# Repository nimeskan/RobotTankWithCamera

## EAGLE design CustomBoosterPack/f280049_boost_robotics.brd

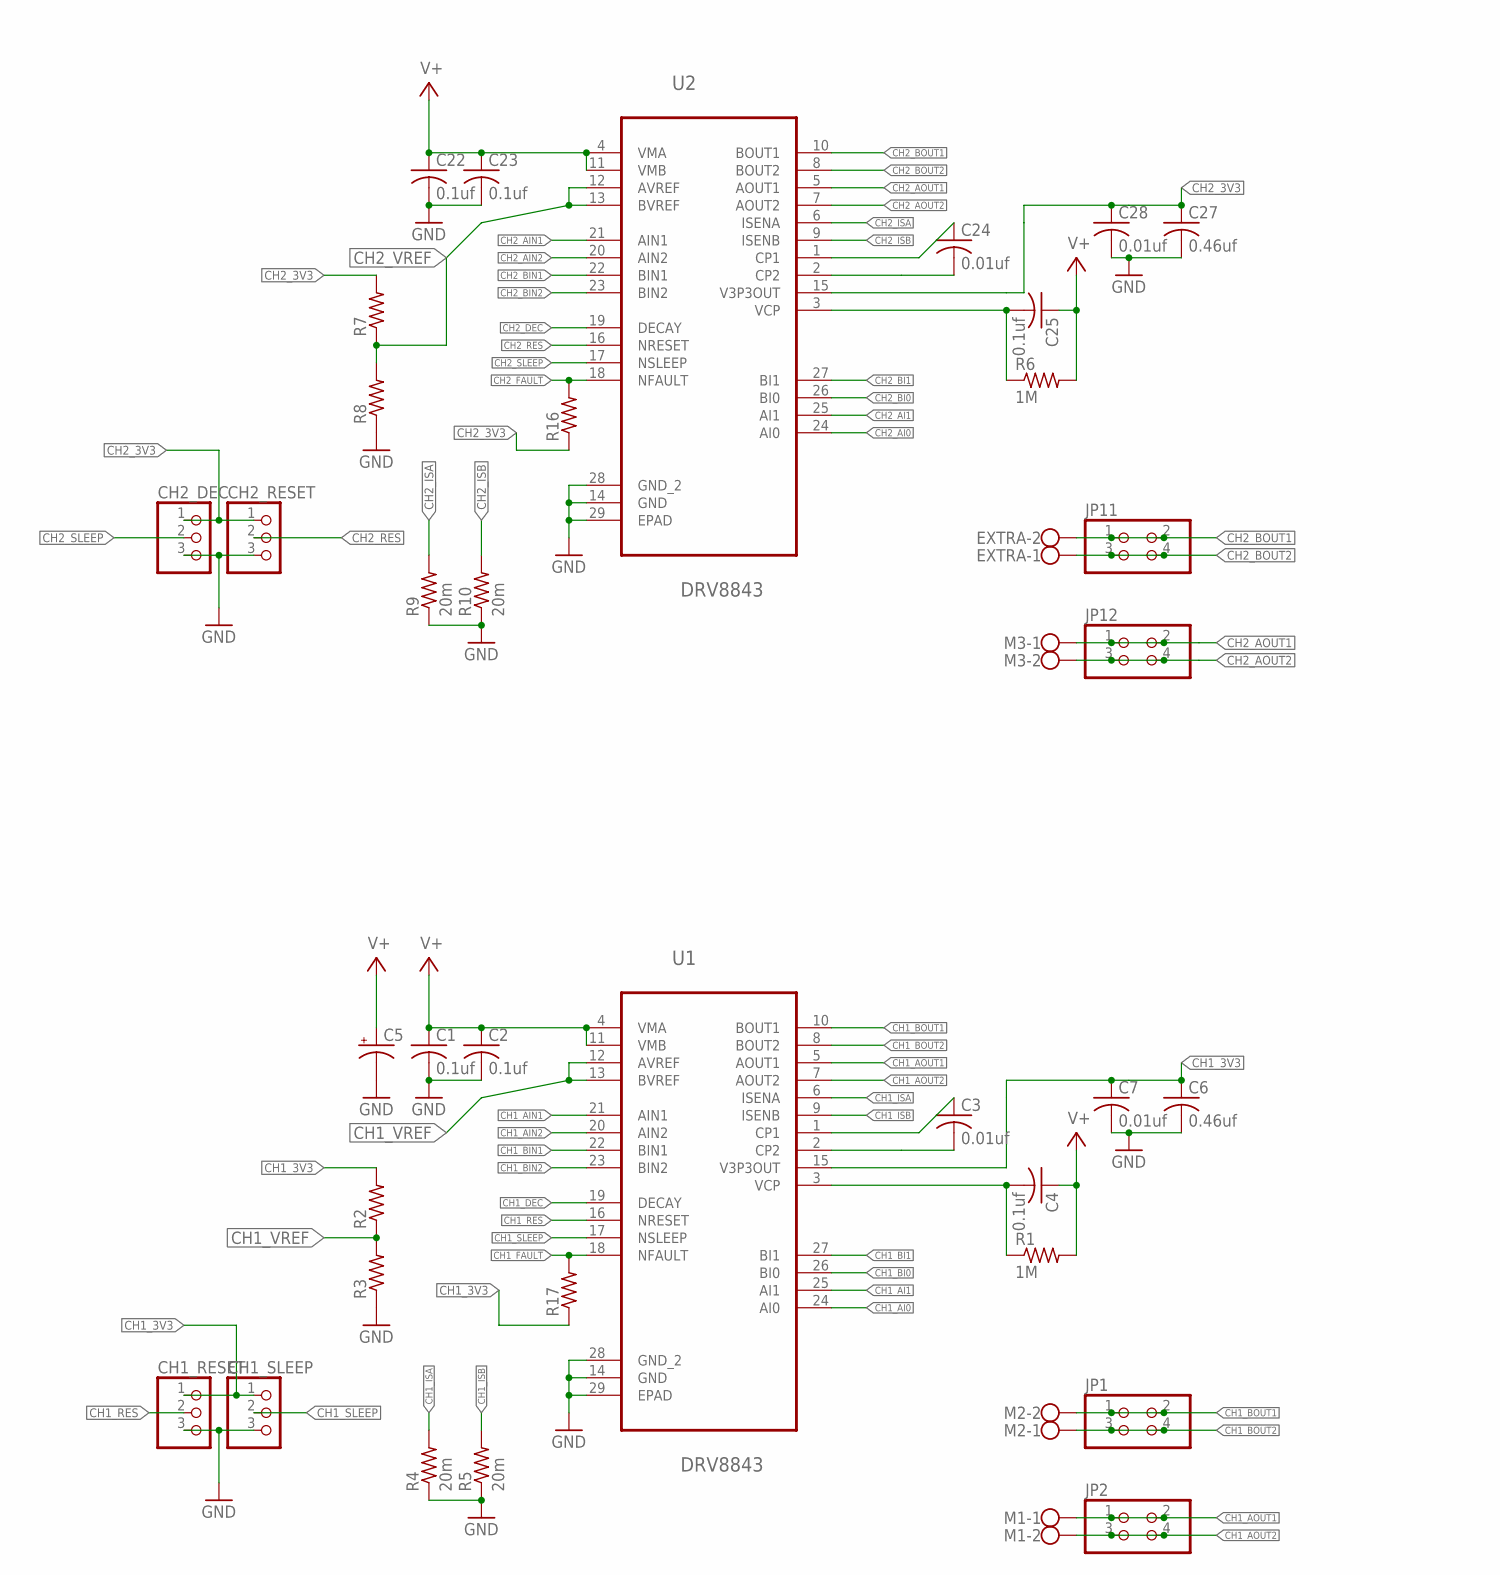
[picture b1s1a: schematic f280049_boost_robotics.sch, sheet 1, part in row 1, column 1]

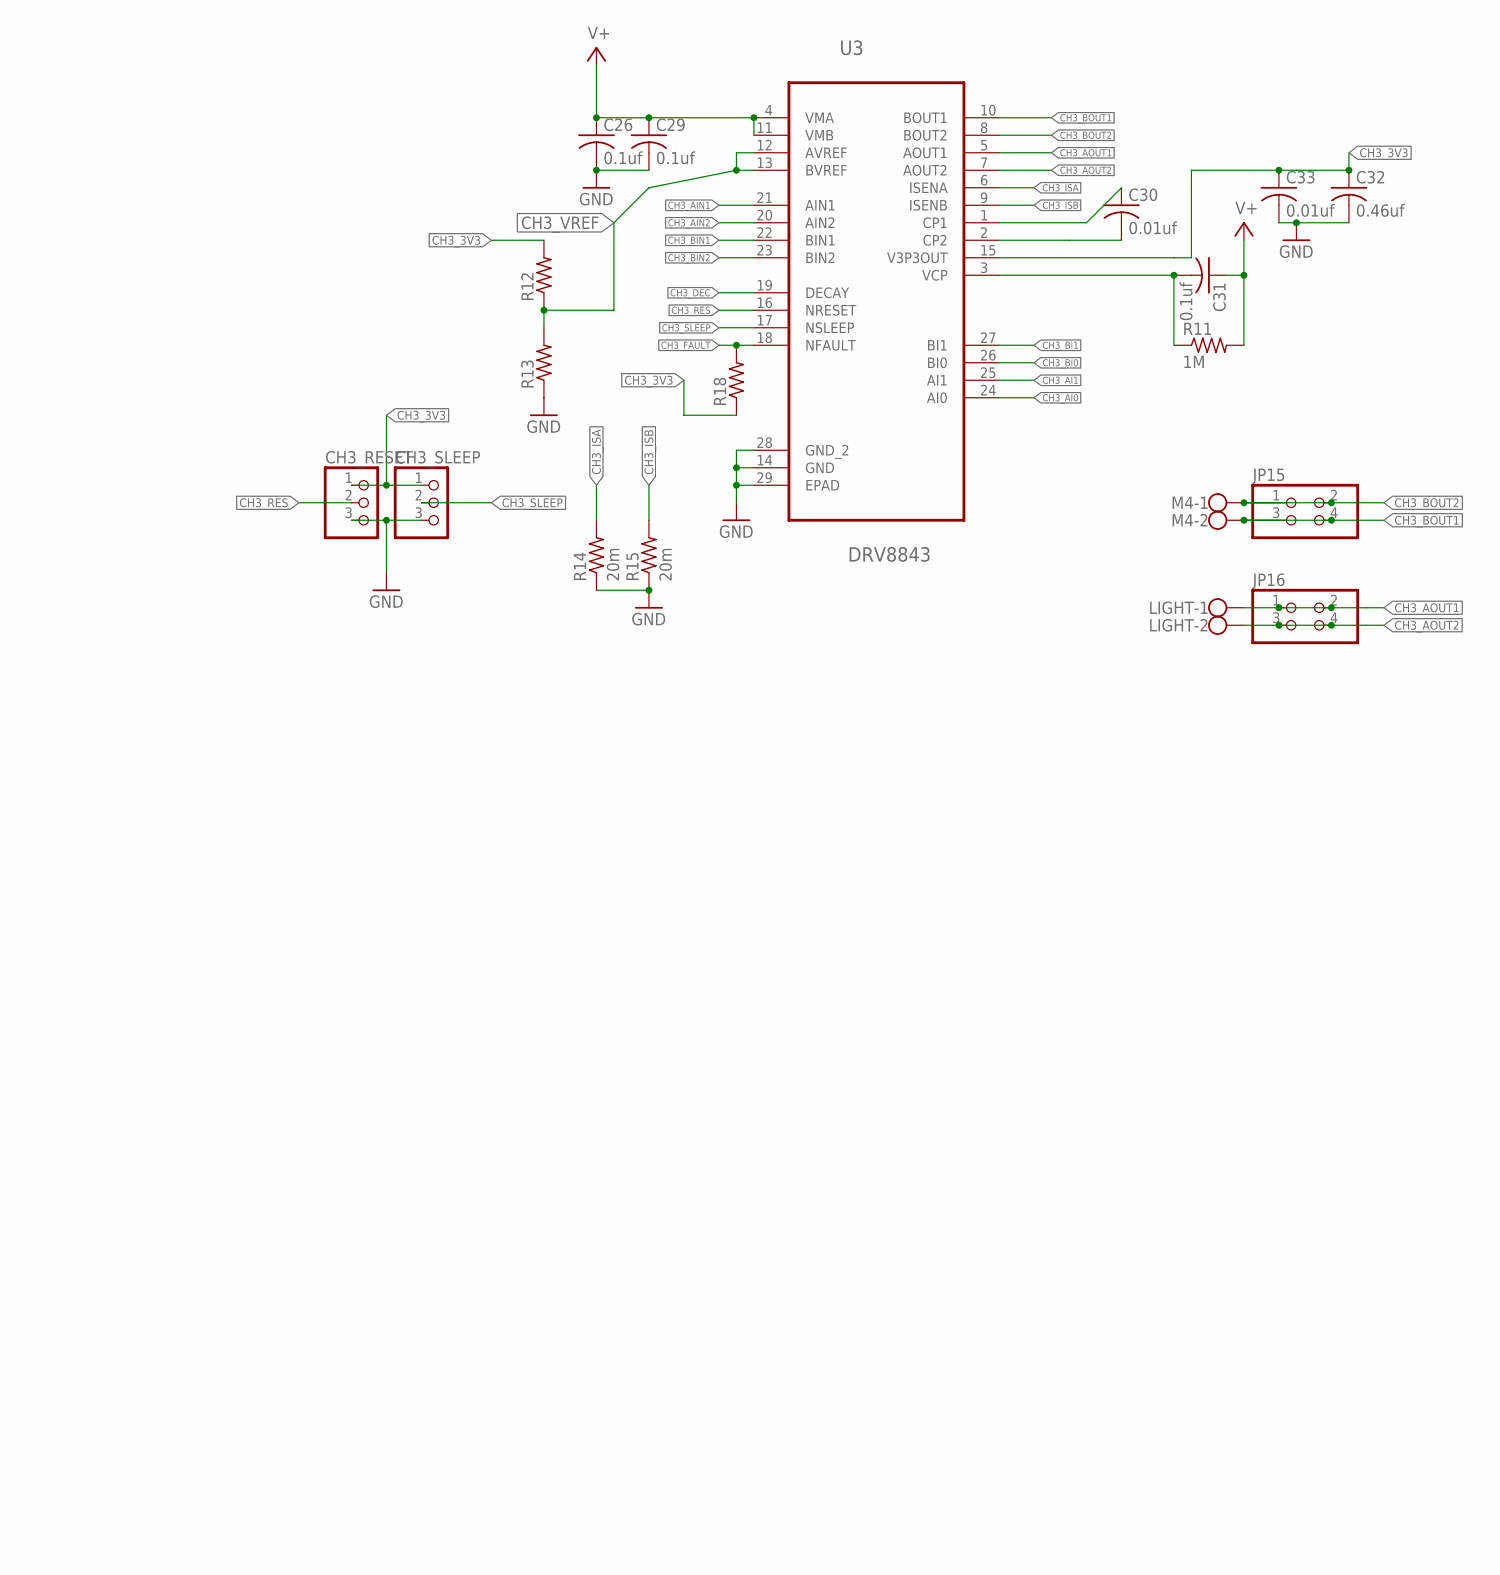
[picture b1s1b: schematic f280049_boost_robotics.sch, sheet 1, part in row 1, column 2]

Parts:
C1, C2, C4, C22, C23, C25, C26, C29, C31: 0.1uf; C0603K
C3, C7, C24, C28, C30, C33: 0.01uf; C0603K
C5: CPOL-USE5-8.5; E5-8,5
C6, C27, C32: 0.46uf; C0603K
CH1_RESET, CH1_SLEEP, CH2_DEC, CH2_RESET, CH3_RESET, CH3_SLEEP: PINHD-1X3; 1X03
EXTRA: W237-102
JP1, JP2, JP11, JP12, JP15, JP16: PINHD-2X2; 2X02
LIGHT: W237-102
M1, M2, M3, M4: W237-102
R1, R6, R11: 1M; R0402
R2, R3, R7, R8, R12, R13, R16, R17, R18: R-US_R0402; R0402
R4, R5, R9, R10, R14, R15: 20m; R0402
U1, U2, U3: DRV8843; SOP65P640X120-29N

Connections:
CH1_3V3: C6.1, C7.1, CH1_RESET.1, CH1_SLEEP.1, R2.2, R17.1, U1.15 (V3P3OUT)
CH1_AI0: U1.24 (AI0); also elsewhere on the board
CH1_AI1: U1.25 (AI1); also elsewhere on the board
CH1_AIN1: U1.21 (AIN1); also elsewhere on the board
CH1_AIN2: U1.20 (AIN2); also elsewhere on the board
CH1_AOUT1: JP2.1, JP2.2, M1.1, U1.5 (AOUT1)
CH1_AOUT2: JP2.3, JP2.4, M1.2, U1.7 (AOUT2)
CH1_BI0: U1.26 (BI0); also elsewhere on the board
CH1_BI1: U1.27 (BI1); also elsewhere on the board
CH1_BIN1: U1.22 (BIN1); also elsewhere on the board
CH1_BIN2: U1.23 (BIN2); also elsewhere on the board
CH1_BOUT1: JP1.1, JP1.2, M2.2, U1.10 (BOUT1)
CH1_BOUT2: JP1.3, JP1.4, M2.1, U1.8 (BOUT2)
CH1_DEC: U1.19 (DECAY); also elsewhere on the board
CH1_FAULT: R17.2, U1.18 (NFAULT); also elsewhere on the board
CH1_ISA: R4.2, U1.6 (ISENA)
CH1_ISB: R5.2, U1.9 (ISENB)
CH1_RES: CH1_RESET.2, U1.16 (NRESET)
CH1_SLEEP: CH1_SLEEP.2, U1.17 (NSLEEP)
CH1_VREF: R2.1, R3.2, U1.12 (AVREF), U1.13 (BVREF)
CH2_3V3: C27.1, C28.1, CH2_DEC.1, CH2_RESET.1, R7.2, R16.1, U2.15 (V3P3OUT)
CH2_AI0: U2.24 (AI0); also elsewhere on the board
CH2_AI1: U2.25 (AI1); also elsewhere on the board
CH2_AIN1: U2.21 (AIN1); also elsewhere on the board
CH2_AIN2: U2.20 (AIN2); also elsewhere on the board
CH2_AOUT1: JP12.1, JP12.2, M3.1, U2.5 (AOUT1)
CH2_AOUT2: JP12.3, JP12.4, M3.2, U2.7 (AOUT2)
CH2_BI0: U2.26 (BI0); also elsewhere on the board
CH2_BI1: U2.27 (BI1); also elsewhere on the board
CH2_BIN1: U2.22 (BIN1); also elsewhere on the board
CH2_BIN2: U2.23 (BIN2); also elsewhere on the board
CH2_BOUT1: EXTRA.2, JP11.1, JP11.2, U2.10 (BOUT1)
CH2_BOUT2: EXTRA.1, JP11.3, JP11.4, U2.8 (BOUT2)
CH2_DEC: U2.19 (DECAY); also elsewhere on the board
CH2_FAULT: R16.2, U2.18 (NFAULT); also elsewhere on the board
CH2_ISA: R9.2, U2.6 (ISENA)
CH2_ISB: R10.2, U2.9 (ISENB)
CH2_RES: CH2_RESET.2, U2.16 (NRESET)
CH2_SLEEP: CH2_DEC.2, U2.17 (NSLEEP)
CH2_VREF: R7.1, R8.2, U2.12 (AVREF), U2.13 (BVREF)
CH3_3V3: C32.1, C33.1, CH3_RESET.1, CH3_SLEEP.1, R12.2, R18.1, U3.15 (V3P3OUT)
CH3_AI0: U3.24 (AI0)
CH3_AI1: U3.25 (AI1)
CH3_AIN1: U3.21 (AIN1); also elsewhere on the board
CH3_AIN2: U3.20 (AIN2); also elsewhere on the board
CH3_AOUT1: JP16.1, JP16.2, LIGHT.1, U3.5 (AOUT1)
CH3_AOUT2: JP16.3, JP16.4, LIGHT.2, U3.7 (AOUT2)
CH3_BI0: U3.26 (BI0)
CH3_BI1: U3.27 (BI1)
CH3_BIN1: U3.22 (BIN1); also elsewhere on the board
CH3_BIN2: U3.23 (BIN2); also elsewhere on the board
CH3_BOUT1: JP15.3, JP15.4, M4.2, U3.10 (BOUT1)
CH3_BOUT2: JP15.1, JP15.2, M4.1, U3.8 (BOUT2)
CH3_DEC: U3.19 (DECAY); also elsewhere on the board
CH3_FAULT: R18.2, U3.18 (NFAULT); also elsewhere on the board
CH3_ISA: R14.2, U3.6 (ISENA)
CH3_ISB: R15.2, U3.9 (ISENB)
CH3_RES: CH3_RESET.2, U3.16 (NRESET)
CH3_SLEEP: CH3_SLEEP.2, U3.17 (NSLEEP)
CH3_VREF: R12.1, R13.2, U3.12 (AVREF), U3.13 (BVREF)
GND: C1.2, C2.2, C5.-, C6.2, C7.2, C22.2, C23.2, C26.2, C27.2, C28.2, C29.2, C32.2, C33.2, CH1_RESET.3, CH1_SLEEP.3, CH2_DEC.3, CH2_RESET.3, CH3_RESET.3, CH3_SLEEP.3, R3.1, R4.1, R5.1, R8.1, R9.1, R10.1, R13.1, R14.1, R15.1, U1.14 (GND), U1.28 (GND_2), U1.29 (EPAD), U2.14 (GND), U2.28 (GND_2), U2.29 (EPAD), U3.14 (GND), U3.28 (GND_2), U3.29 (EPAD); also elsewhere on the board
unnamed: C3.1, U1.1 (CP1)
unnamed: C3.2, U1.2 (CP2)
unnamed: C4.2, R1.1, U1.3 (VCP)
unnamed: C24.1, U2.1 (CP1)
unnamed: C24.2, U2.2 (CP2)
unnamed: C25.2, R6.1, U2.3 (VCP)
unnamed: C30.1, U3.1 (CP1)
unnamed: C30.2, U3.2 (CP2)
unnamed: C31.2, R11.1, U3.3 (VCP)
V+: C1.1, C2.1, C4.1, C5.+, C22.1, C23.1, C25.1, C26.1, C29.1, C31.1, R1.2, R6.2, R11.2, U1.4 (VMA), U1.11 (VMB), U2.4 (VMA), U2.11 (VMB), U3.4 (VMA), U3.11 (VMB); also elsewhere on the board

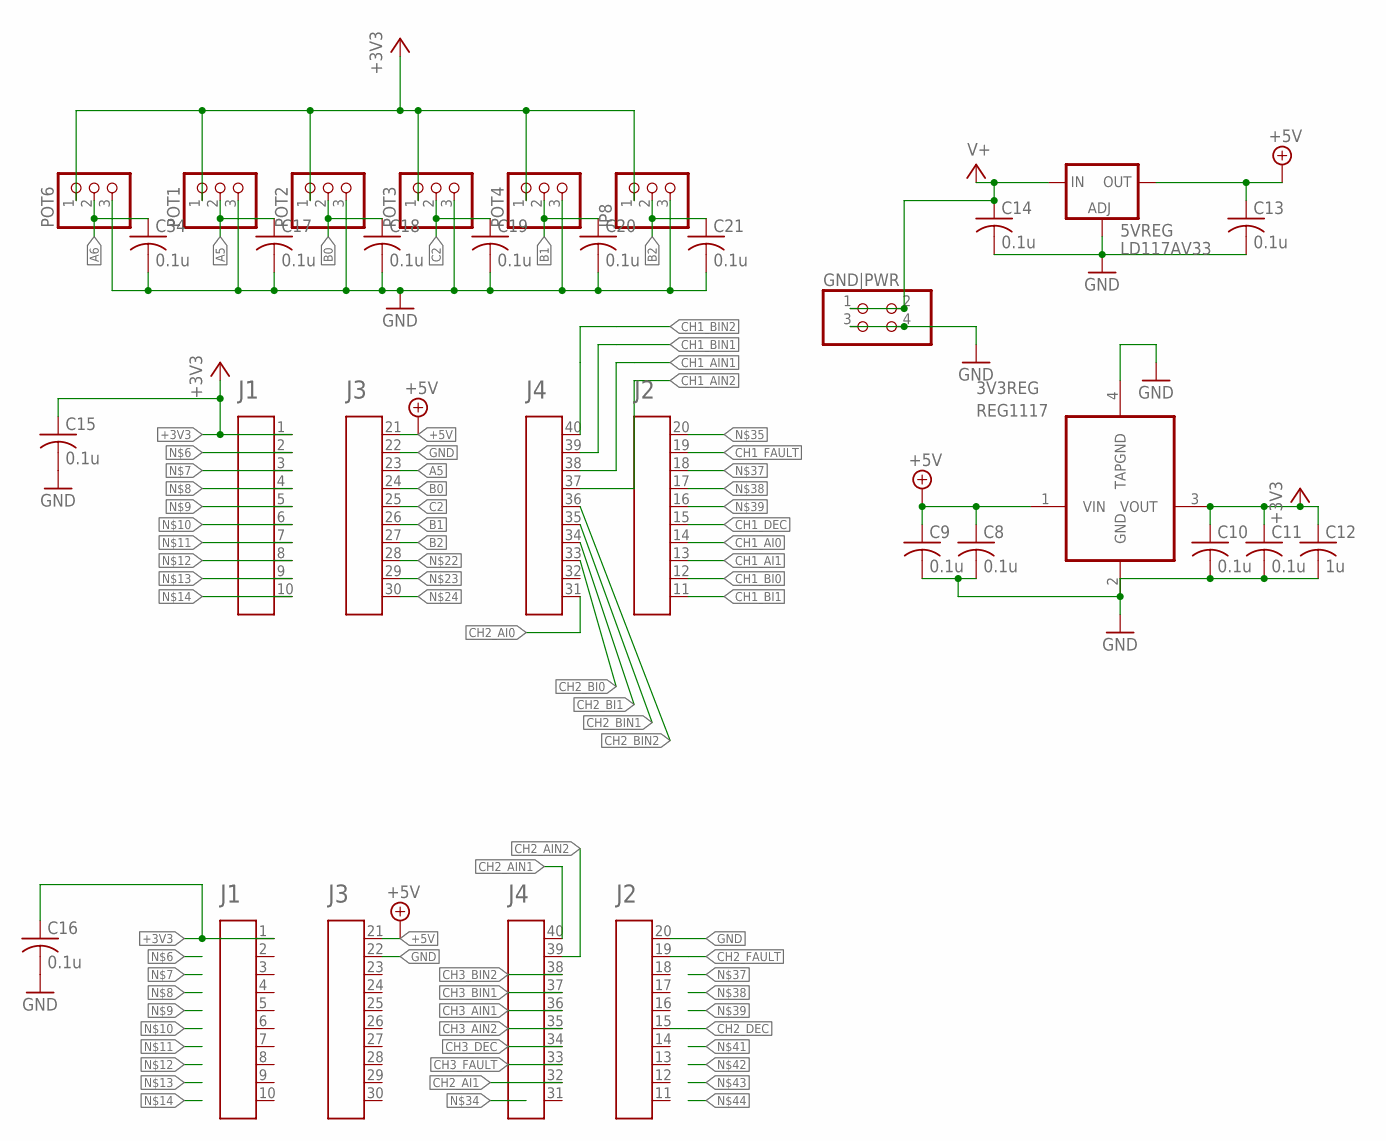
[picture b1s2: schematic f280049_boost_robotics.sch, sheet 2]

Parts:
3V3REG: REG1117; SOT223
5VREG: LD117AV33; TO220L1
A1, A2: HEADER4X10-BOOSTERPACK; 4X10-BOOSTERPACK
C8, C9, C10, C11, C13, C14, C15, C16, C17, C18, C19, C20, C21, C34: 0.1u; C0603K
C12: 1u; C0805K
GND|PWR: PINHD-2X2; 2X02
JP8: PINHD-1X3; 1X03
POT1, POT2, POT3, POT4, POT6: PINHD-1X3; 1X03

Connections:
+3V3: 3V3REG.3 (VOUT), A1.1, A2.1, C10.1, C11.1, C12.1, C15.1, C16.1, JP8.1, POT1.1, POT2.1, POT3.1, POT4.1, POT6.1
+5V: 3V3REG.1 (VIN), 5VREG.2 (OUT), A1.21, A2.21, C8.1, C9.1, C13.1
A5: A2.23, C17.1, POT1.2
A6: C34.1, POT6.2
B0: A2.24, C18.1, POT2.2
B1: A2.26, C20.1, POT4.2
B2: A2.27, C21.1, JP8.2
C2: A2.25, C19.1, POT3.2
CH1_AI0: A2.14; also elsewhere on the board
CH1_AI1: A2.13; also elsewhere on the board
CH1_AIN1: A2.38; also elsewhere on the board
CH1_AIN2: A2.37; also elsewhere on the board
CH1_BI0: A2.12; also elsewhere on the board
CH1_BI1: A2.11; also elsewhere on the board
CH1_BIN1: A2.39; also elsewhere on the board
CH1_BIN2: A2.40; also elsewhere on the board
CH1_DEC: A2.15; also elsewhere on the board
CH1_FAULT: A2.19; also elsewhere on the board
CH2_AI0: A2.31; also elsewhere on the board
CH2_AI1: A1.32; also elsewhere on the board
CH2_AIN1: A1.40; also elsewhere on the board
CH2_AIN2: A1.39; also elsewhere on the board
CH2_BI0: A2.33; also elsewhere on the board
CH2_BI1: A2.34; also elsewhere on the board
CH2_BIN1: A2.35; also elsewhere on the board
CH2_BIN2: A2.36; also elsewhere on the board
CH2_DEC: A1.15; also elsewhere on the board
CH2_FAULT: A1.19; also elsewhere on the board
CH3_AIN1: A1.36; also elsewhere on the board
CH3_AIN2: A1.35; also elsewhere on the board
CH3_BIN1: A1.37; also elsewhere on the board
CH3_BIN2: A1.38; also elsewhere on the board
CH3_DEC: A1.34; also elsewhere on the board
CH3_FAULT: A1.33; also elsewhere on the board
GND: 3V3REG.2 (GND), 3V3REG.4 (TAPGND), 5VREG.1 (ADJ), A1.20, A1.22, A2.22, C8.2, C9.2, C10.2, C11.2, C12.2, C13.2, C14.2, C15.2, C16.2, C17.2, C18.2, C19.2, C20.2, C21.2, C34.2, GND|PWR.3, GND|PWR.4, JP8.3, POT1.3, POT2.3, POT3.3, POT4.3, POT6.3; also elsewhere on the board
V+: 5VREG.3 (IN), C14.1, GND|PWR.1, GND|PWR.2; also elsewhere on the board

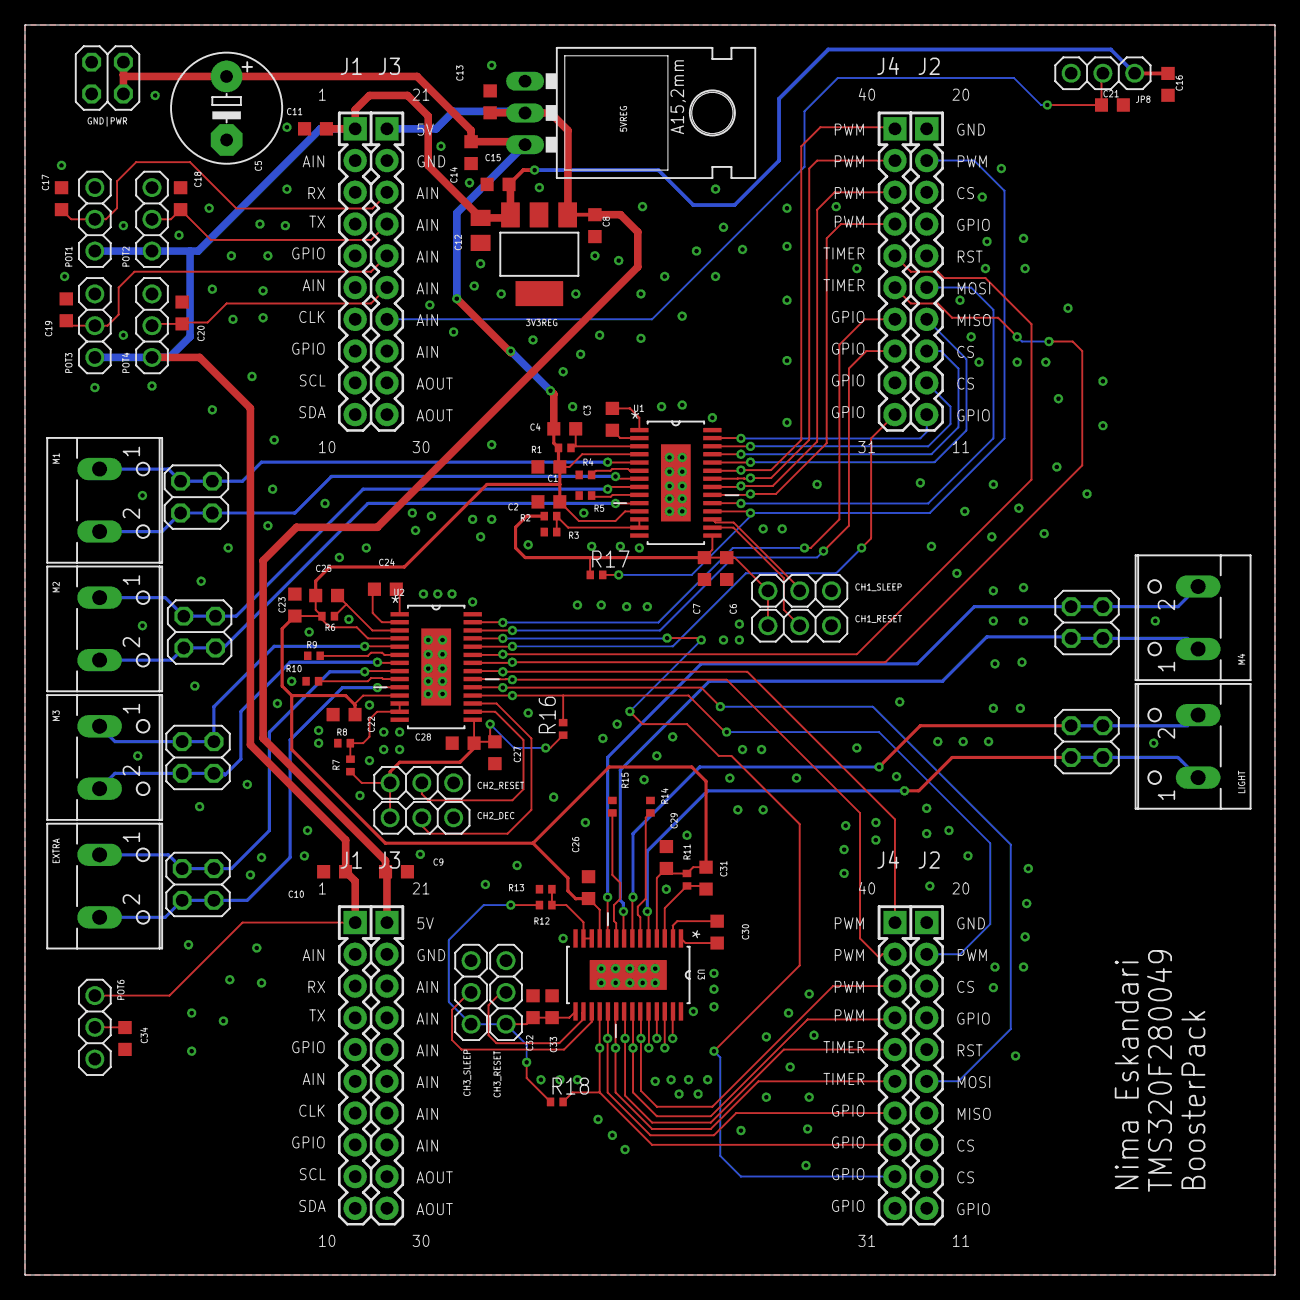
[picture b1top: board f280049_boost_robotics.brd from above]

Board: 2 copper layers, 100.0 x 100.0 mm, 84 parts (0 on the bottom side), 75 nets.

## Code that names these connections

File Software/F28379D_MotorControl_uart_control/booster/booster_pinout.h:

/*
 * booster_pinout.h
 *
 *  Created on: Sep 14, 2018
 *      Author: a0225962
 */

#ifndef BOOSTER_PINOUT_H_
#define BOOSTER_PINOUT_H_

// PINMAP

// CHANNEL1
#define CH1_BIN2                0
#define CH1_BIN1                1

#define CH1_AIN2                3
#define CH1_AIN1                2

#define CH1_DEC                 58
#define CH1_FAULT               61

#define CH1_BI1                 29
#define CH1_BI0                 125

#define CH1_AI1                 124
#define CH1_AI0                 59

#define CH1_BIN2_CONFIG         GPIO_0_EPWM1A
#define CH1_BIN1_CONFIG         GPIO_1_EPWM1B

#define CH1_AIN2_CONFIG         GPIO_3_EPWM2B
#define CH1_AIN1_CONFIG         GPIO_2_EPWM2A

#define CH1_DEC_CONFIG          GPIO_58_GPIO58
#define CH1_FAULT_CONFIG        GPIO_61_GPIO61

#define CH1_BI1_CONFIG          GPIO_29_GPIO29
#define CH1_BI0_CONFIG          GPIO_125_GPIO125

#define CH1_AI1_CONFIG          GPIO_124_GPIO124
#define CH1_AI0_CONFIG          GPIO_59_GPIO59

// CHANNEL 2
#define CH2_BIN2                4
#define CH2_BIN1                5

#define CH2_AIN2                6
#define CH2_AIN1                7

#define CH2_DEC                 63
#define CH2_FAULT               66

#define CH2_BI1                 24
#define CH2_BI0                 16

//#define CH2_AI1                 DAC3
//#define CH2_AI0                 DAC2

#define CH2_BIN2_CONFIG         GPIO_4_EPWM3A
#define CH2_BIN1_CONFIG         GPIO_5_EPWM3B

#define CH2_AIN2_CONFIG         GPIO_6_EPWM4A
#define CH2_AIN1_CONFIG         GPIO_7_EPWM4B

#define CH2_DEC_CONFIG          GPIO_63_GPIO63
#define CH2_FAULT_CONFIG        GPIO_66_GPIO66

#define CH2_BI1_CONFIG          GPIO_24_GPIO24
#define CH2_BI0_CONFIG          GPIO_16_GPIO16

//#define CH2_AI1_CONFIG          GPIO_14_GPIO14
//#define CH2_AI0_CONFIG          GPIO_25_GPIO25

// CHANNEL 3
#define CH3_BIN2                8
#define CH3_BIN1                9

#define CH3_AIN2                11
#define CH3_AIN1                10

#define CH3_DEC                 14
#define CH3_FAULT               15

#define CH3_BIN2_CONFIG         GPIO_8_EPWM5A
#define CH3_BIN1_CONFIG         GPIO_9_EPWM5B

#define CH3_AIN2_CONFIG         GPIO_11_EPWM6B
#define CH3_AIN1_CONFIG         GPIO_10_EPWM6A

#define CH3_DEC_CONFIG          GPIO_14_GPIO14
#define CH3_FAULT_CONFIG        GPIO_15_GPIO15

// EQEPs
// Channel1
#define CH1_EQEPA               20
#define CH1_EQEPB               21
#define CH1_EQEPI               99

#define CH2_EQEPA               54
#define CH2_EQEPB               55
#define CH2_EQEPI               57

#define CH1_EQEPA_CONFIG        GPIO_20_EQEP1A
#define CH1_EQEPB_CONFIG        GPIO_21_EQEP1B
#define CH1_EQEPI_CONFIG        GPIO_99_EQEP1I

#define CH2_EQEPA_CONFIG        GPIO_54_EQEP2A
#define CH2_EQEPB_CONFIG        GPIO_55_EQEP2B
#define CH2_EQEPI_CONFIG        GPIO_57_EQEP2I

void booster_Pinout_init();


#endif /* BOOSTER_PINOUT_H_ */

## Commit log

2018-11-29 Initial commit with Final Project Files
